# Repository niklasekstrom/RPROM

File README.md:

# RPROM

RPROM is a ROM emulator for 16 bit Amiga computers (A500, A600, A2000) based on
the RP2350B microcontroller. RPROM was designed in collaboration by
[Niklas Ekström](https://github.com/niklasekstrom/) and
[Per Bengtsson](https://github.com/RetroNynjah).

The RPROM board has a 4 MB SPI flash memory. Each ROM image is 512 kB in size,
and therefore the 4 MB is divided into eight *slots* of 512 kB each. The first
slot is dedicated to store code and configuration data for the RP2350B. The
seven remaining slots are used to store ROM images.

ROM images can be written to flash memory either via USB, or directly from the
Amiga using a program called `RPROM`. This `RPROM` program is also used to
switch which slot is the *active slot*.

This repository contains the [hardware](Hardware), [firmware](Firmware) and
[software](Software) for RPROM. The design is intended to be easily
understandable and hackable. For example, the firmware is built from a single,
roughly 500 lines long, [source code file](Firmware/rprom.c).

## The RPROM command

`RPROM` is a CLI command that runs on the Amiga. It has the following
subcommands:

- `RPROM status` prints status information about the device
- `RPROM switch <slot>` switches the active slot and reboots the Amiga
- `RPROM write <slot> <image>` writes the content of file `<image>` to
slot `<slot>`
- `RPROM read <slot> <image>` reads the content of slot `<slot>` and saves it
to file `<image>`
- `RPROM erase <slot>` erases slot `<slot>`

Note that ROM images should *not* be byte swapped.

## Programming using USB

Both the firmware and ROM images can be programmed from a PC using USB.
Programming is done using the `picotool` program, which can be downloaded from
https://github.com/raspberrypi/pico-sdk-tools/releases. The RP2350B
microcontroller needs to first be in download mode. To put the RP2350B in
download mode, hold down the BOOTSEL button on the board, and then click the
RUN button. The microcontroller should show up as a USB drive on your PC.

To program the firmware, run `picotool load rprom.uf2`.

To write a ROM image to a slot, run `picotool load <image> -t bin -o <addr>`,
where `<addr>` depends on the slot:

- slot 1: `0x10080000`
- slot 2: `0x10100000`
- slot 3: `0x10180000`
- slot 4: `0x10200000`
- slot 5: `0x10280000`
- slot 6: `0x10300000`
- slot 7: `0x10380000`

## Hardware revisions

There are two revisions of the hardware. The difference between the revisions is
quite minor. For rev2, the OE and CE signals have moved from gpio pins 36 and 35
to pins 16 and 17. The benefit of this is that both PIOs with gpiobase=0 and
gpiobase=16 can read the OE and CE signals. This in turn results in that using
rev2, the time from when the Amiga negates the OE signal to when the RPROM
tri-states the data bus is a small number of nanoseconds shorter. In most cases
this won't make any difference. In any case, if you are ordering new RPROM PCBs
then you likely prefer the latest revision.

## Compiling the firmware

In order to compile the firmware you need a recent version (e.g. 2.2.0 or later)
of the [pico-sdk](https://github.com/raspberrypi/pico-sdk).

Note that there is a `RPROM_REV` compile definition in
[Firmware/CMakeLists.txt](Firmware/CMakeLists.txt) that should be equal to the
hardware revision that the firmware should be used with. Make sure you set it to
the correct value.

## License

This design is free for non-comercial use. The designers take no responsibility
for if it doesn't work or if it causes damage to your equipment. If you want to
build boards to sell then you need to first ask for approval from the designers.

## Bill of materials (BOM)

| References | Value | Footprint | LCSC Part | Quantity |
|------------|-------|-----------|-----------|----------|
| C2, C8, C11, C12, C13, C14, C15, C16, C17, C18, C20, C21 | 100n | C_0402_1005Metric | C1525 | 12 |
| C1, C5, C19 | 10u | C_0805_2012Metric | C15850 | 3 |
| C3, C4 | 15p | C_0402_1005Metric | C1548 | 2 |
| C6, C7, C9, C10 | 4.7u | C_0402_1005Metric | C23733 | 4 |
| R2, R4, R6 | 1k | R_0402_1005Metric | C11702 | 3 |
| R7, R8 | 27 | R_0402_1005Metric | C25092 | 2 |
| R1 | 10k | R_0402_1005Metric | C25744 | 1 |
| R3 | 33 | R_0402_1005Metric | C25105 | 1 |
| L1 | 3.3u | L_pol_2016 | C42411119 | 1 |
| D1, D2 | B5819W_SL | D_SOD-123 | C8598 | 2 |
| U1 | RP2350_80QFN | RP2350-QFN-80-1EP_10x10_P0.4mm_EP3.4x3.4mm | C42415655 | 1 |
| U2 | TLV1117-33 | SOT-223-3_TabPin2 | C15578 | 1 |
| Y1 | ABM8-272-T3 | Crystal_SMD_3225-4Pin_3.2x2.5mm | C20625731 | 1 |
| SW1, SW2 | SW_Push | SW_SPST_TS-1088 | C720477 | 2 |
| IC1 | W25Q32RVXHJQ *or* ZD25WQ32CEIGR | Winbond_USON-8-1EP_3x2mm_P0.5mm_EP0.2x1.6mm | C5258281 | 1 |
| J1 | USB_B_Micro | USB_Micro-B_Amphenol_10103594-0001LF_Horizontal | C428495 | 1 |
| J2, J3 | Conn_01x20 | PinHeader_1x20_P2.54mm_Vertical | - | 2 |
| J4 | Conn_01x01 | PinHeader_1x01_P2.54mm_Horizontal | - | 1 |

## Building

The hardware can be cheaply built by [JLCPCB](https://jlcpcb.com/) using
Economic PCBA. Components should be assembled only on the top side, and select
that tooling holes are "Added by Customer".

Please pay attention to the orientation of the components if ordering assembly
from JLCPCB. Especially pay attention to the orientation of coil L1. When
uploading the component placement file to JLCPCB I had to manually fix the
orientation of L1 regardless of what the component placement file specified.

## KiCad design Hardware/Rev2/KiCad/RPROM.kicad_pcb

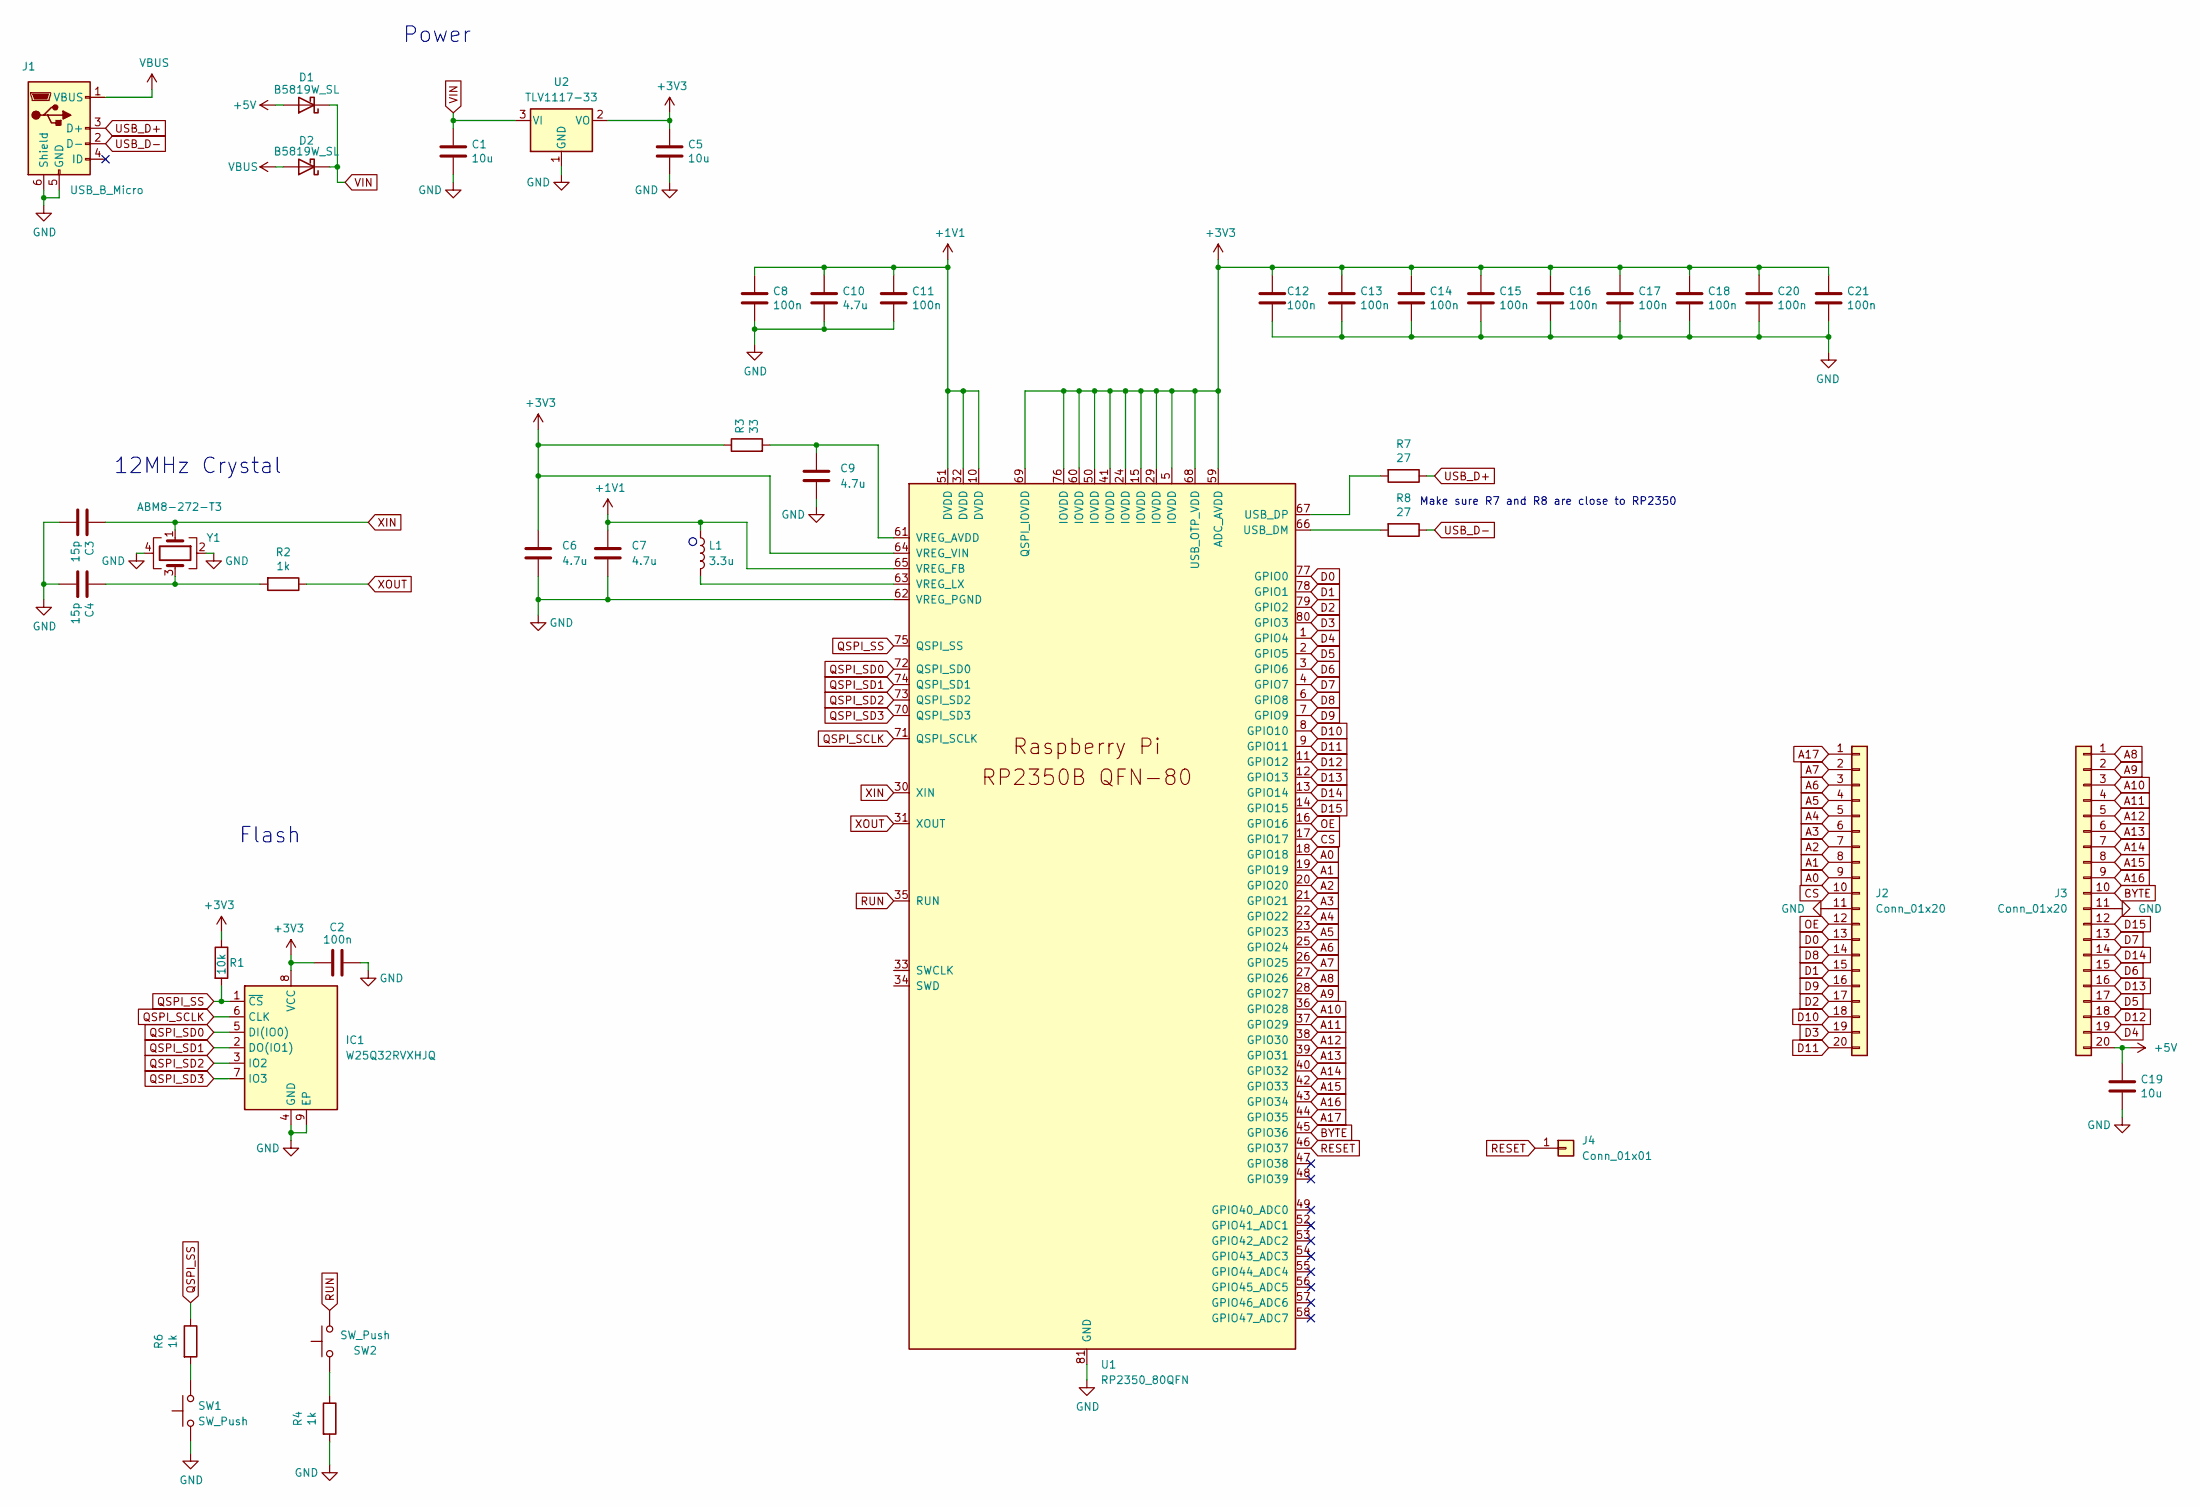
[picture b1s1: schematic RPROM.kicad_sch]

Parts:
C1, C5, C19: 10u; C_0805_2012Metric
C2, C8, C11, C12, C13, C14, C15, C16, C17, C18, C20, C21: 100n; C_0402_1005Metric
C3, C4: 15p; C_0402_1005Metric
C6, C7: 4.7u; C_0402_1005Metric_small_pads
C9, C10: 4.7u; C_0402_1005Metric
D1, D2: B5819W_SL; D_SOD-123
IC1: W25Q32RVXHJQ; Winbond_USON-8-1EP_3x2mm_P0.5mm_EP0.2x1.6mm
J1: USB_B_Micro; USB_Micro-B_Amphenol_10103594-0001LF_Horizontal
J2, J3: Conn_01x20; PinHeader_1x20_P2.54mm_Vertical
J4: Conn_01x01; PinHeader_1x01_P2.54mm_Vertical
L1: 3.3u; L_pol_2016
R1: 10k; R_0402_1005Metric
R2, R4, R6: 1k; R_0402_1005Metric
R3: 33; R_0402_1005Metric
R7, R8: 27; R_0402_1005Metric
SW1, SW2: SW_Push; SW_SPST_TS-1088
U1: RP2350_80QFN; RP2350-QFN-80-1EP_10x10_P0.4mm_EP3.4x3.4mm_ThermalVias
U2: TLV1117-33; SOT-223-3_TabPin2
Y1: ABM8-272-T3; Crystal_SMD_3225-4Pin_3.2x2.5mm

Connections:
+1V1: C7.1, C8.1, C10.1, C11.1, L1.1, U1.10 (DVDD), U1.32 (DVDD), U1.51 (DVDD), U1.65 (VREG_FB)
+3V3: C2.1, C5.1, C6.1, C12.1, C13.1, C14.1, C15.1, C16.1, C17.1, C18.1, C20.1, C21.1, IC1.8 (VCC), R1.1, R3.1, U1.5 (IOVDD), U1.15 (IOVDD), U1.24 (IOVDD), U1.29 (IOVDD), U1.41 (IOVDD), U1.50 (IOVDD), U1.59 (ADC_AVDD), U1.60 (IOVDD), U1.64 (VREG_VIN), U1.68 (USB_OTP_VDD), U1.69 (QSPI_IOVDD), U1.76 (IOVDD), U2.2 (VO)
+5V: C19.1, D1.2 (A), J3.20
A0: J2.9, U1.18 (GPIO18)
A1: J2.8, U1.19 (GPIO19)
A2: J2.7, U1.20 (GPIO20)
A3: J2.6, U1.21 (GPIO21)
A4: J2.5, U1.22 (GPIO22)
A5: J2.4, U1.23 (GPIO23)
A6: J2.3, U1.25 (GPIO24)
A7: J2.2, U1.26 (GPIO25)
A8: J3.1, U1.27 (GPIO26)
A9: J3.2, U1.28 (GPIO27)
A10: J3.3, U1.36 (GPIO28)
A11: J3.4, U1.37 (GPIO29)
A12: J3.5, U1.38 (GPIO30)
A13: J3.6, U1.39 (GPIO31)
A14: J3.7, U1.40 (GPIO32)
A15: J3.8, U1.42 (GPIO33)
A16: J3.9, U1.43 (GPIO34)
A17: J2.1, U1.44 (GPIO35)
BYTE: J3.10, U1.45 (GPIO36)
CS: J2.10, U1.17 (GPIO17)
D0: J2.13, U1.77 (GPIO0)
D1: J2.15, U1.78 (GPIO1)
D2: J2.17, U1.79 (GPIO2)
D3: J2.19, U1.80 (GPIO3)
D4: J3.19, U1.1 (GPIO4)
D5: J3.17, U1.2 (GPIO5)
D6: J3.15, U1.3 (GPIO6)
D7: J3.13, U1.4 (GPIO7)
D8: J2.14, U1.6 (GPIO8)
D9: J2.16, U1.7 (GPIO9)
D10: J2.18, U1.8 (GPIO10)
D11: J2.20, U1.9 (GPIO11)
D12: J3.18, U1.11 (GPIO12)
D13: J3.16, U1.12 (GPIO13)
D14: J3.14, U1.13 (GPIO14)
D15: J3.12, U1.14 (GPIO15)
GND: C1.2, C2.2, C3.2, C4.2, C5.2, C6.2, C7.2, C8.2, C9.2, C10.2, C11.2, C12.2, C13.2, C14.2, C15.2, C16.2, C17.2, C18.2, C19.2, C20.2, C21.2, IC1.4 (GND), IC1.9 (EP), J1.5 (GND), J1.6 (Shield), J2.11, J3.11, R4.2, SW1.1, U1.62 (VREG_PGND), U1.81 (GND), U2.1 (GND), Y1.2, Y1.4
unnamed: C4.1, R2.2, Y1.3
unnamed: R4.1, SW2.1
unnamed: R6.2, SW1.2
unnamed: R8.2, U1.66 (USB_DM)
unnamed: R7.2, U1.67 (USB_DP)
unnamed: C9.1, R3.2, U1.61 (VREG_AVDD)
unnamed: L1.2, U1.63 (VREG_LX)
OE: J2.12, U1.16 (GPIO16)
QSPI_SCLK: IC1.6 (CLK), U1.71 (QSPI_SCLK)
QSPI_SD0: IC1.5 (DI(IO0)), U1.72 (QSPI_SD0)
QSPI_SD1: IC1.2 (DO(IO1)), U1.74 (QSPI_SD1)
QSPI_SD2: IC1.3 (IO2), U1.73 (QSPI_SD2)
QSPI_SD3: IC1.7 (IO3), U1.70 (QSPI_SD3)
QSPI_SS: IC1.1 (~CS), R1.2, R6.1, U1.75 (QSPI_SS)
RESET: J4.1, U1.46 (GPIO37)
RUN: SW2.2, U1.35 (RUN)
USB_D+: J1.3 (D+), R7.1
USB_D-: J1.2 (D-), R8.1
VBUS: D2.2 (A), J1.1 (VBUS)
VIN: C1.1, D1.1 (K), D2.1 (K), U2.3 (VI)
XIN: C3.1, U1.30 (XIN), Y1.1
XOUT: R2.1, U1.31 (XOUT)

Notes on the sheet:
12MHz Crystal
Make sure R7 and R8 are close to RP2350
Flash
Power

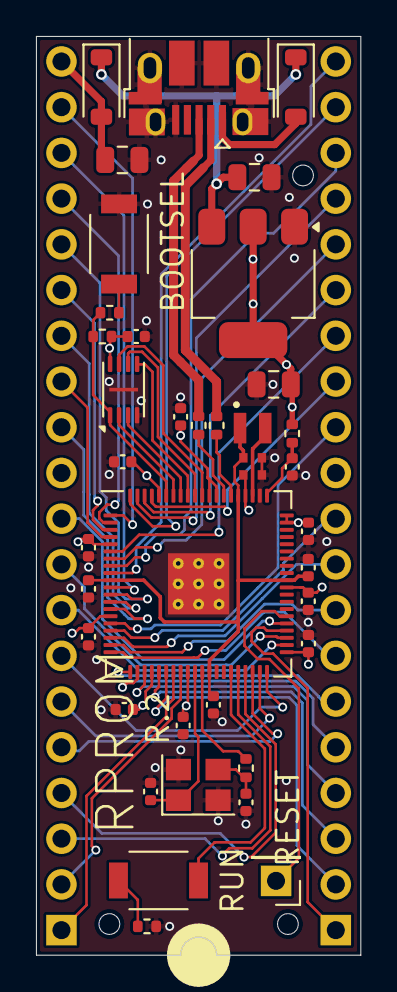
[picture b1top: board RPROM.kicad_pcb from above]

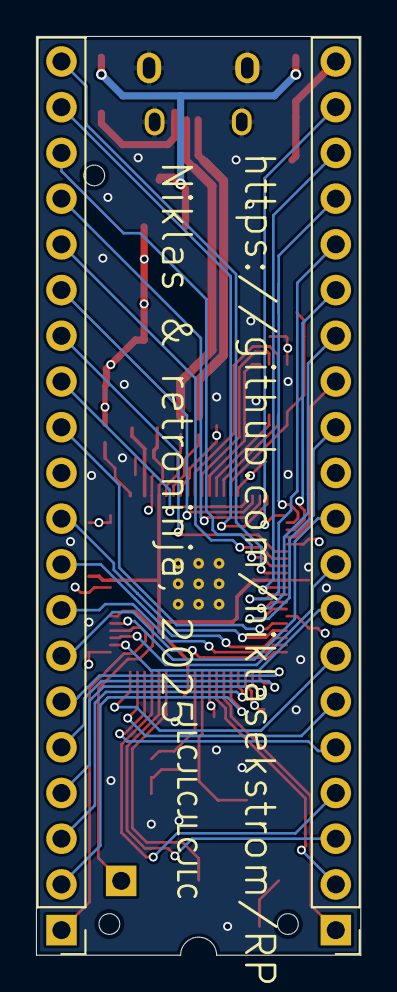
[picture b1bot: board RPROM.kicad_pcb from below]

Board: 4 copper layers, 18.0 x 51.0 mm, 41 parts (2 on the bottom side), 62 nets.

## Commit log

2025-08-16 Move switch to core1
2025-08-16 Move all read handling to core1
2025-08-17 Add slot config to flash
2025-08-17 Add automatic detection of rev5 vs rev6 motherboards
2025-08-17 Rename folders
2025-08-17 Add symbolic constants
2025-08-17 Add minor refactorings
2025-08-23 Add the ability to write images to flash from Amiga
    Also update CMakeLists.txt to remove unused functionality from build.
2025-09-01 Make write command automatically erase slot first
2025-09-04 Add hardware rev 1
2025-09-05 Add copyright messages to source code files
2025-09-05 Add start of a README
2025-09-05 Add missing fclose calls
2025-09-05 Reboot by software after switching
2025-09-07 Add accurate 500 ms delay
2025-09-08 Update KiCad design to use correct flash component
2025-09-08 Add instructions for programming via USB
2025-09-09 Add bill of materials (BOM) to readme
2025-09-11 Add development credits
2025-09-14 Reorder RPROM subcommands
2025-09-14 Add description of RPROM subcommands to README
2025-09-18 Add finalized StatusV1 struct
    Adding a magic number to the beginning of the struct was proposed by
    nicode (https://github.com/nicodex).
2025-09-18 Refactor shared protocol definitions to protocol.h
2025-09-27 Add recovery switcher
2025-10-02 Set PICO_HEAP_SIZE to zero
    The firmware on the RP2350B isn't doing dynamic memory allocations
    (malloc/free), so there is no need to set aside memory for a heap.
    Removing the heap prohibits printf debugging over USB.
2025-10-02 Add photo of installed RPROM
2025-10-08 Add paragraph about economic pcba to README
2025-10-18 Add ability to hold reset to cycle active rom slot
2025-10-31 Add version string to RPROM command
2025-11-24 Signal failures through DOS return code
2025-12-17 Make tristating faster after OE is negated
2025-12-21 Implement update rom slot on reset hold feature
    Added functionality to trigger an update rom slot on reset hold for a specified duration.
2025-12-23 Fix typo to mask out the lower 14 bits
    By chance the typo didn't cause an actual problem even though the
    masking was incorrect.
    Reported by Nico Bendlin
2025-12-23 Make reboot procedure compatible with Diagrom
2026-04-12 Add PIO support instead of CPU bitbang
2026-04-12 Add reset pin handling for switching active slot
2026-04-12 Add firmware support for hardware rev2
2026-04-12 Add hardware rev2
    The difference between rev1 and rev2 is that the OE and CE pins are
    moved from gpio pins 36 and 35 to pins 16 and 17. This is done so that
    both PIOs with gpiobase=0 and gpiobase=16 can access the OE and CE pins.
